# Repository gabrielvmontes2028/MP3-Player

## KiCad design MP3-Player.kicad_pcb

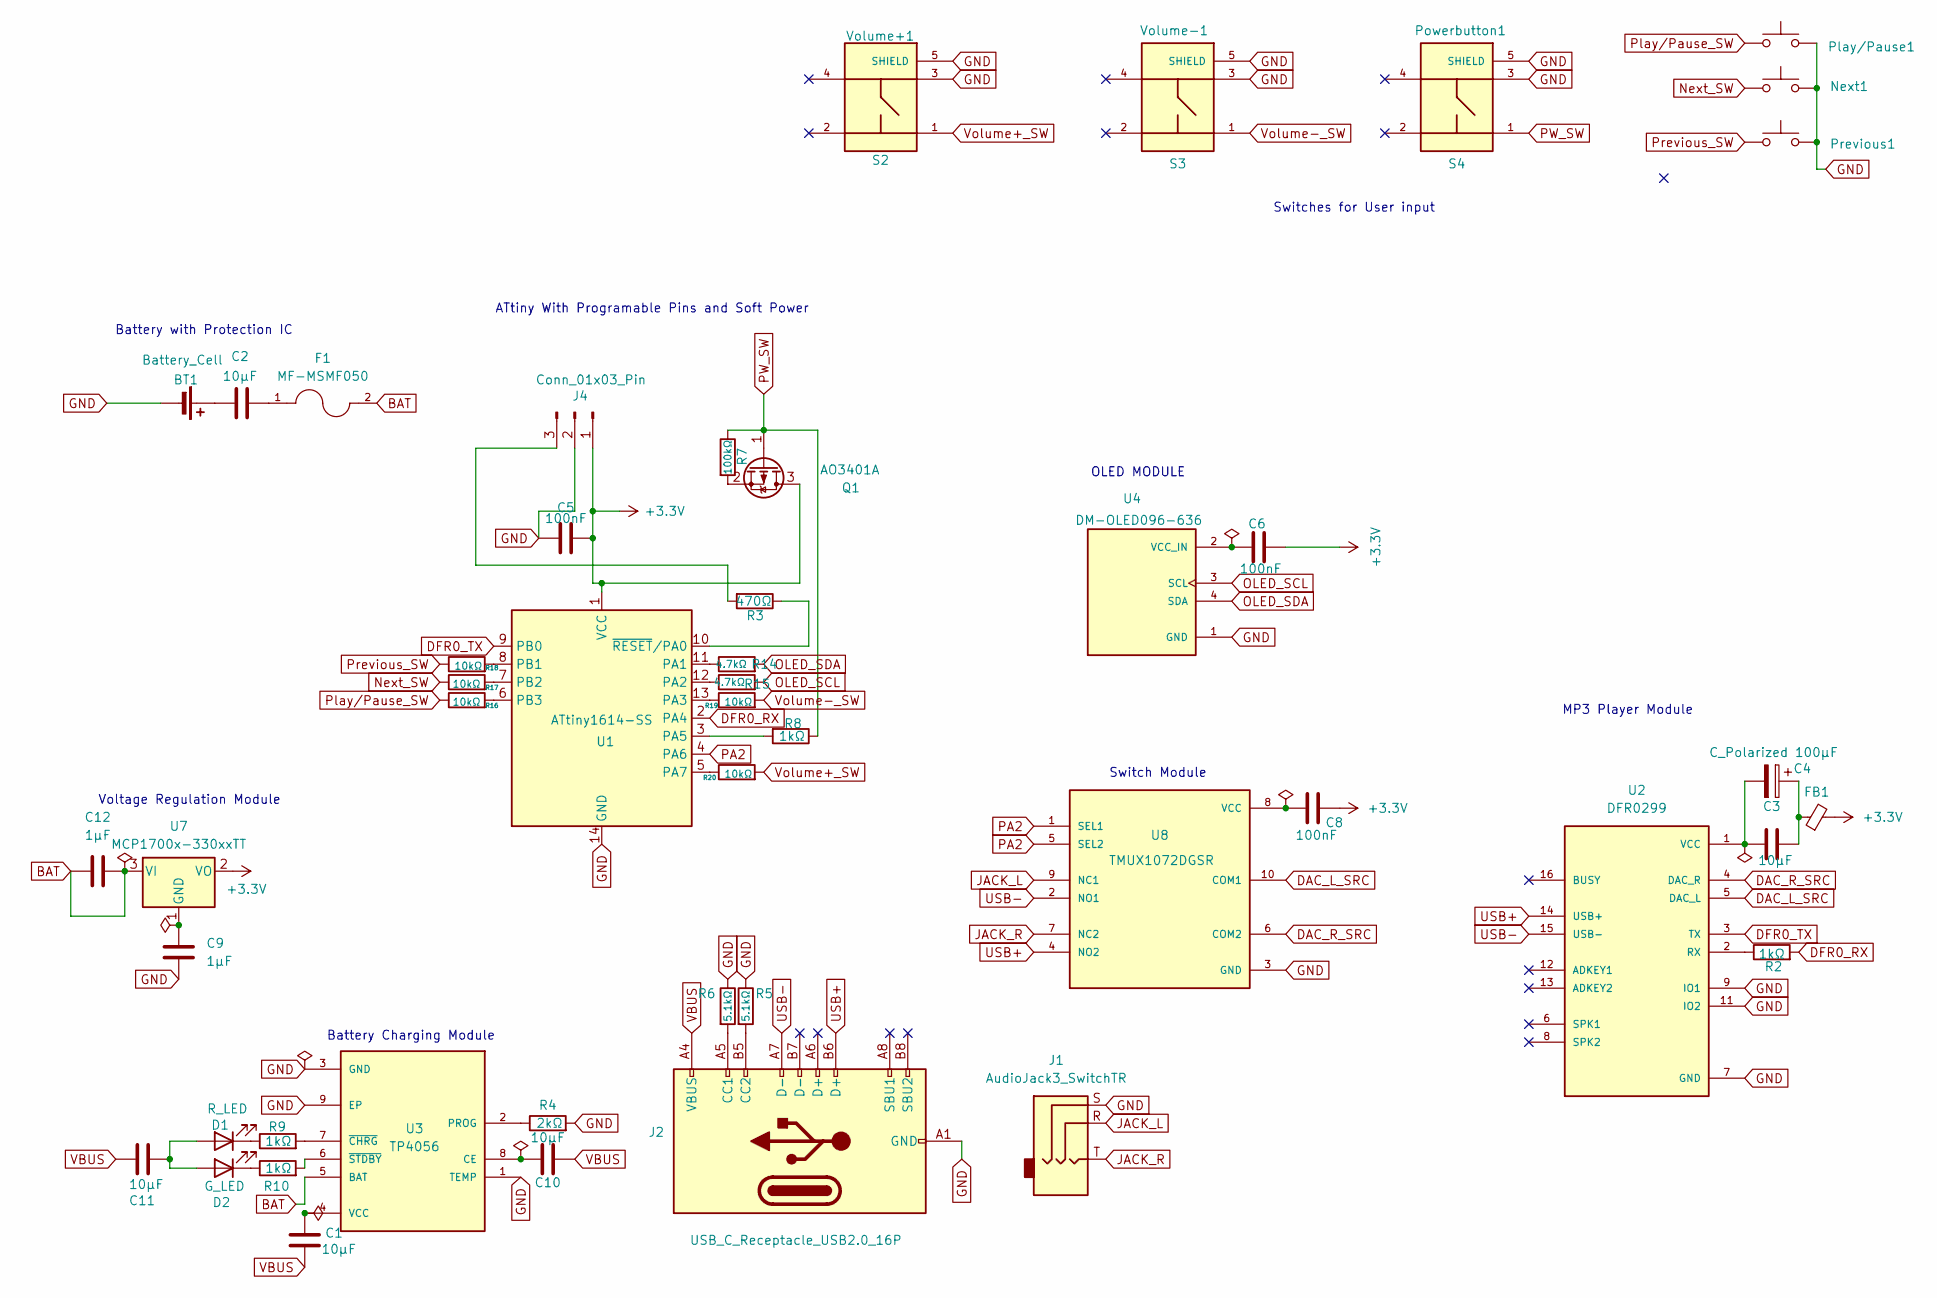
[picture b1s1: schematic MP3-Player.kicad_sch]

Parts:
BT1: Battery_Cell; PinHeader_1x02_P2.54mm_Vertical
C1, C2, C10, C11: 10μF; C_0805_2012Metric
C3: 10µF; C_0805_2012Metric
C4: C_Polarized 100µF; CP_Elec_4x5.4
C5, C6, C8: 100nF; C_0805_2012Metric
C9, C12: 1μF; C_0805_2012Metric
D1: R_LED; LED_0603_1608Metric
D2: G_LED; LED_0603_1608Metric
F1: MF-MSMF050; FUSER_MF-MSMF050
FB1: FerriteBead_Small; L_0603_1608Metric
J1: AudioJack3_SwitchTR; Jack_3.5mm_CUI_SJ1-3523N_Horizontal
J2: USB_C_Receptacle_USB2.0_16P; USB_C_Receptacle_Palconn_UTC16-G
J4: Conn_01x03_Pin; PinHeader_1x03_P2.54mm_Vertical
Next1: SW_Push; KSA_Tactile_SPST
Play/Pause1: SW_Push; KSA_Tactile_SPST
Powerbutton1: S4; SW_PTS840GMSMTRLFS
Previous1: SW_Push; KSA_Tactile_SPST
Q1: AO3401A; SOT-23
R2, R8, R9, R10: 1kΩ; R_0805_2012Metric
R3: 470Ω; R_0805_2012Metric
R4: 2kΩ; R_0805_2012Metric
R5, R6: 5.1kΩ; R_0805_2012Metric
R7: 100kΩ; R_0805_2012Metric
R14, R15: 4.7kΩ; R_0805_2012Metric
R16, R17, R18, R19, R20: 10kΩ; R_0805_2012Metric
S2: Volume+1; SW_PTS840GMSMTRLFS
U1: ATtiny1614-SS; SOIC-14_3.9x8.7mm_P1.27mm
U2: DFR0299; MODULE_DFR0299
U3: TP4056; SOP127P600X175-9N
U4: DM-OLED096-636; MODULE_DM-OLED096-636; PARTREV 2018-09-10
U7: MCP1700x-330xxTT; SOT-23
U8: TMUX1072DGSR; TSSOP-10_3x3mm_P0.5mm; PARTREV C
Volume-1: S3; SW_PTS840GMSMTRLFS

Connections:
+3.3V: C5.1, C6.1, C8.2, FB1.2, J4.1, Q1.3 (D), U1.1 (VCC), U7.2 (VO)
BAT: C12.1, C12.2, F1.2, U3.5 (BAT), U7.3 (VI)
DAC_L_SRC: U2.5 (DAC_L), U8.10 (COM1)
DAC_R_SRC: U2.4 (DAC_R), U8.6 (COM2)
DFR0_RX: R2.2, U1.2 (PA4)
DFR0_TX: U1.9 (PB0), U2.3 (TX)
GND: BT1.2 (-), C5.2, C9.2, J1.S, J2.A1 (GND), J2.A12 (GND), J2.B1 (GND), J2.B12 (GND), J4.2, Next1.2, Play/Pause1.2, Powerbutton1.3, Powerbutton1.5 (SHIELD_5), Previous1.2, R4.2, R5.1, R6.1, S2.3, S2.5 (SHIELD_5), U1.14 (GND), U2.7 (GND), U2.9 (IO1), U2.10 (GND), U2.11 (IO2), U3.1 (TEMP), U3.3 (GND), U3.9 (EP), U4.1 (GND), U8.3 (GND), Volume-1.3, Volume-1.5 (SHIELD_5)
JACK_L: J1.R, U8.9 (NC1)
JACK_R: J1.T, U8.7 (NC2)
unnamed: BT1.1 (+), C2.2
unnamed: C2.1, F1.1
unnamed: C3.2, C4.1, FB1.1
unnamed: C11.1, D1.2 (A), D2.2 (A)
unnamed: D1.1 (K), R9.1
unnamed: D2.1 (K), R10.1
unnamed: J2.A5 (CC1), R6.2
unnamed: J2.B5 (CC2), R5.2
unnamed: J4.3, R3.2
unnamed: Q1.2 (S), R7.2
unnamed: R14.1, U1.11 (PA1)
unnamed: R15.1, U1.12 (PA2)
unnamed: R19.1, U1.13 (PA3)
unnamed: R8.2, U1.3 (PA5)
unnamed: R20.1, U1.5 (PA7)
unnamed: R18.2, U1.8 (PB1)
unnamed: R17.2, U1.7 (PB2)
unnamed: R16.2, U1.6 (PB3)
unnamed: R3.1, U1.10 (~RESET/PA0)
unnamed: R2.1, U2.2 (RX)
unnamed: C3.1, C4.2, U2.1 (VCC)
unnamed: C10.1, U3.8 (CE)
unnamed: R4.1, U3.2 (PROG)
unnamed: C1.1, U3.4 (VCC)
unnamed: R9.2, U3.7 (~CHRG)
unnamed: R10.2, U3.6 (~STDBY)
unnamed: C6.2, U4.2 (VCC_IN)
unnamed: C9.1, U7.1 (GND)
unnamed: C8.1, U8.8 (VCC)
Next_SW: Next1.1, R17.1
OLED_SCL: R15.2, U4.3 (SCL)
OLED_SDA: R14.2, U4.4 (SDA)
PA2: U1.4 (PA6), U8.1 (SEL1), U8.5 (SEL2)
PW_SW: Powerbutton1.1, Q1.1 (G), R7.1, R8.1
Play/Pause_SW: Play/Pause1.1, R16.1
Previous_SW: Previous1.1, R18.1
USB+: J2.B6 (D+), U2.14 (USB+), U8.4 (NO2)
USB-: J2.A7 (D-), U2.15 (USB-), U8.2 (NO1)
VBUS: C1.2, C10.2, C11.2, J2.A4 (VBUS), J2.A9 (VBUS), J2.B4 (VBUS), J2.B9 (VBUS)
Volume+_SW: R20.2, S2.1
Volume-_SW: R19.2, Volume-1.1

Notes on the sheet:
MP3 Player Module
ATtiny With Programable Pins and Soft Power
Switches for User input
Battery Charging Module
OLED MODULE
Battery with Protection IC
Switch Module
Voltage Regulation Module

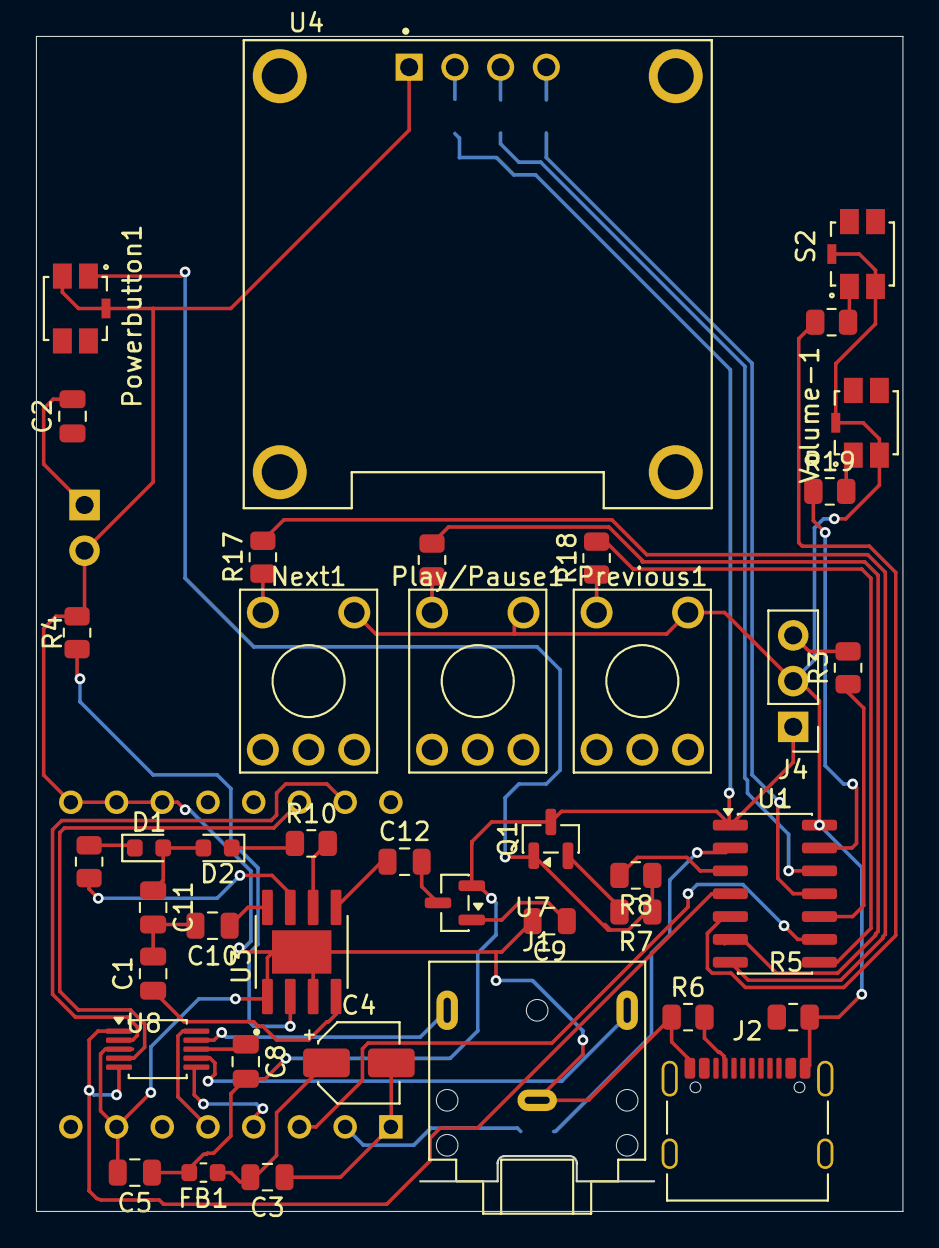
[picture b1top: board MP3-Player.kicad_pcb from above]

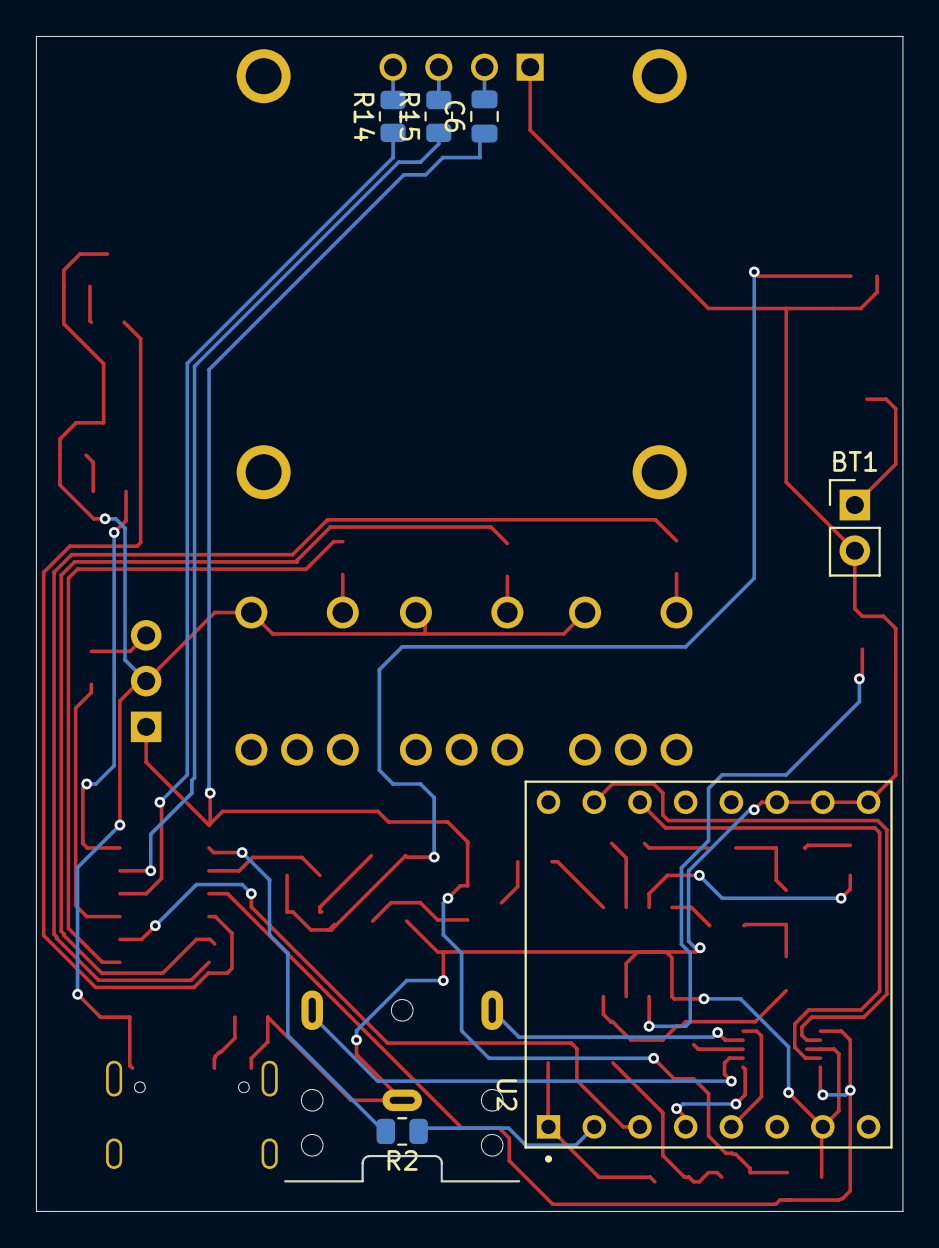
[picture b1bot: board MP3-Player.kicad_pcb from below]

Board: 2 copper layers, 48.1 x 65.2 mm, 47 parts (6 on the bottom side), 49 nets.

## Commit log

2026-06-19 Custom Parts
    Custom Parts needed for the MP3-Player
